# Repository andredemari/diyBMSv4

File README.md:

# ESP32 port of diyBMS v4

This is my port of Stuart Pittaway's excellent diyBMS ver 4 project

In this port the ESP8266 Controller has been replaced by an ESP32 and various changes have been made to support my local needs.
If you are looking for a straight port to ESP32 of Stuart's project, check out the 'Vanilla' branch.
Note: Because of the way serial ports work in ESP32, the Cell module firmware from this fork must be used. Cell modules programmed with the original firmware will not work.

Main changes are :-
* New Controller PCB design with ESP32 module ( a Lolin 32 Lite easily available on AliExpress)
* INA226 Current and Voltage monitor on PCB - INA226 is able to measure current through an external shunt on high or low side of battery. It supports battery voltages of up to 36V,
so since my battery is more than that I put the shunt halfway up the battery stack, and use a voltage divider to measure total battery voltage. INA226 is I2C connected to the ESP32.
https://www.ti.com/lit/ds/symlink/ina226.pdf
* I2C connector to attach to various fan controllers.
* PWM connector to signal discharge rate to my inverter.
* Serial interface to signal charge rate to my BST900 charger [BST900(https://github.com/delboy711/BST900)]
* Two connectors for Solid State Relays to power on/off charger and inverter.
* Management of Controller via MQTT commands from Node-Red.

Stuart's original README follows

##################################################################
 
Version 4 of the diyBMS

Do it yourself battery management system for Lithium ion battery packs/cells

If you are looking for version 3 of this project take a look here https://github.com/stuartpittaway/diyBMS

# TRAVIS-CI

# Videos on how to use and build

https://www.youtube.com/stuartpittaway

# WARNING

This is a DIY product/solution so don’t use this for safety critical systems or in any situation where there could be a risk to life.  

There is no warranty, it may not work as expected or at all.

The use of this project is done so entirely at your own risk.  It may involve electrical voltages which could kill - if in doubt, seek help.

The use of this project may not be compliant with local laws or regulations - if in doubt, seek help.

# License

This work is licensed under a Creative Commons Attribution-NonCommercial-ShareAlike 2.0 UK: England & Wales License.

https://creativecommons.org/licenses/by-nc-sa/2.0/uk/

You are free to:
* Share — copy and redistribute the material in any medium or format
* Adapt — remix, transform, and build upon the material
The licensor cannot revoke these freedoms as long as you follow the license terms.

Under the following terms:
* Attribution — You must give appropriate credit, provide a link to the license, and indicate if changes were made. You may do so in any reasonable manner, but not in any way that suggests the licensor endorses you or your use.
* Non-Commercial — You may not use the material for commercial purposes.
* ShareAlike — If you remix, transform, or build upon the material, you must distribute your contributions under the same license as the original.
* No additional restrictions — You may not apply legal terms or technological measures that legally restrict others from doing anything the license permits.

Notices:
You do not have to comply with the license for elements of the material in the public domain or where your use is permitted by an applicable exception or limitation.

No warranties are given. The license may not give you all of the permissions necessary for your intended use. For example, other rights such as publicity, privacy, or moral rights may limit how you use the material.

# Problem

A DIY Powerwall is the DIY construction of a pack of battery cells to create an energy store which can be used via inverters to power electrical items in the home. Generally cells are salvaged/second hand, and typically use Lithium 18650 cells.

Lithium batteries need to be kept at the same voltage level across a parallel pack. This is done by balancing each cell in the pack to raise or lower its voltage to match the others.

Existing balancing solutions are available in the market place, but at a relatively high cost compared to the cost of the battery bank, so this project is to design a low-cost, simple featured BMS/balancer.

# BMS Design

Design Goals: 
* Build upon my existing skill set and knowledge. 
* Building something that others can contribute to using regular standard libraries and off the shelf components.
* Build something that is inheriently safe
* Use platform.io to manage code and libraries
* Use Arduino based libraries and tools 
* Put everything on GITHUB
* Document it (always gets left to the end!)

# How it works

Controller provides human interface over Wifi/Web and also integrates with other systems like MQTT, emonCMS and Grafana.

Controller is esp8266-12e (NodeMCU v1) - although could be upgraded to ESP32 if really needed.

Controller should be able to take action on alerts/events to shut down inverters/chargers/fuses.

Each cell in a battery pack has a monitoring module.  This uses AVR ATTINY841 linked together by optoisolated serial ports for communication.

ATTINY841 provides:
* internal temperature monitoring
* external temperature monitoring
* Spare input/output for 3rd party use
* autonomous cell voltage balancing - it should still work even if controller is down

# How as v4 improved over v3?

* Code is better!
* Web interface no longer requires access to internet to download javascript libraries
* Controller provides outputs for integration with relay boards and switch gear
* Rules to control relay outputs
* Cell modules use ATTINY841 chip which provides more pins and lower power usage
* Removal of 3.3v regulator and ADUM chips lowers current usage significantly
* v3 module uses 10-12mA current constantly and v4 uses <1mA
* Dual temperature monitoring board + cells

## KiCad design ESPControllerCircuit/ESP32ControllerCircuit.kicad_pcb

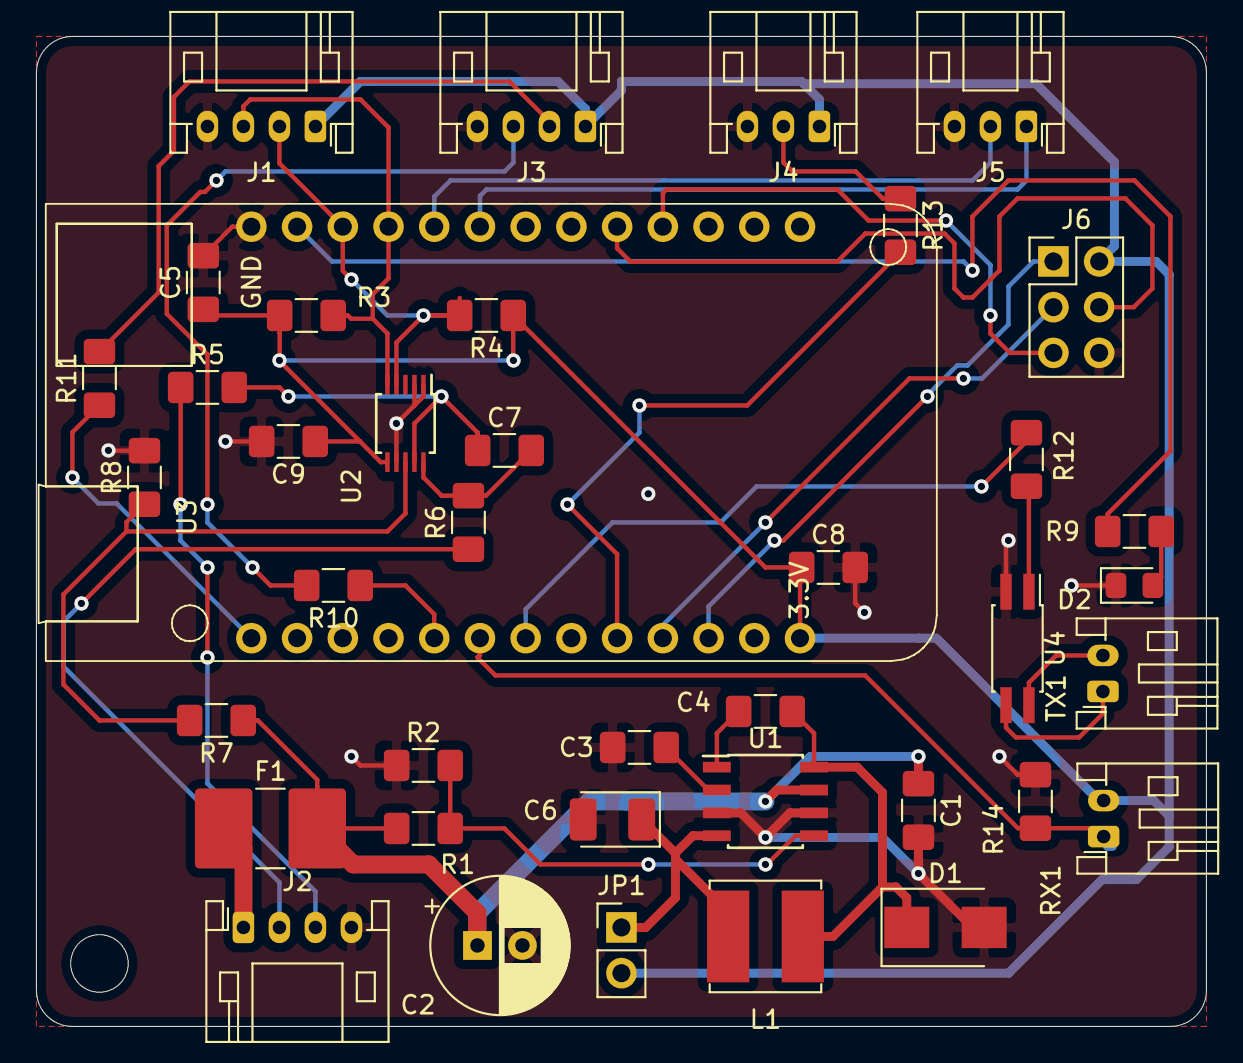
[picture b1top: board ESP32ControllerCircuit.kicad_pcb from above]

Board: 2 copper layers, 65.0 x 55.0 mm, 40 parts (0 on the bottom side), 35 nets.

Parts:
C1, C3, C4, C5, C7, C8, C9: 100nF; C_1206_3216Metric_Pad1.42x1.75mm_HandSolder
C2: 47uF; CP_Radial_D7.5mm_P2.50mm
C6: 47uF Vishay TR3D476K016CO200; CP_EIA-3528-12_Kemet-T_Pad1.50x2.35mm_HandSolder
D1: CD214A-B360LF; D_SMB
D2: COMMS; LED_0805_2012Metric_Pad1.15x1.40mm_HandSolder
F1: 85mA; R_2816_7142Metric_Pad3.20x4.45mm_HandSolder
J1: I2C; JST_PH_S4B-PH-K_1x04_P2.00mm_Horizontal
J2: Battery Sense; JST_PH_S4B-PH-K_1x04_P2.00mm_Horizontal
J3: Inverter/Charger SS Relays; JST_PH_S4B-PH-K_1x04_P2.00mm_Horizontal
J4: Inverter PWM Control; JST_PH_S3B-PH-K_1x03_P2.00mm_Horizontal
J5: BST900 Serial; JST_PH_S3B-PH-K_1x03_P2.00mm_Horizontal
J6: I/O; PinHeader_2x03_P2.54mm_Vertical
JP1: Battery Power; PinHeader_1x02_P2.54mm_Vertical
L1: 150uH; L_Bourns_SRN6045TA
R1: 1M; R_1206_3216Metric_Pad1.42x1.75mm_HandSolder
R2: 390K; R_1206_3216Metric_Pad1.42x1.75mm_HandSolder
R3, R4: 1K; R_1206_3216Metric_Pad1.42x1.75mm_HandSolder
R5, R6: 10R; R_1206_3216Metric_Pad1.42x1.75mm_HandSolder
R7, R8: 100K; R_1206_3216Metric_Pad1.42x1.75mm_HandSolder
R9: 470R; R_1206_3216Metric_Pad1.42x1.75mm_HandSolder
R10, R11: 0R; R_1206_3216Metric_Pad1.42x1.75mm_HandSolder
R12: 220R; R_1206_3216Metric_Pad1.42x1.75mm_HandSolder
R13: 390R; R_1206_3216Metric_Pad1.42x1.75mm_HandSolder
R14: 4K7; R_1206_3216Metric_Pad1.42x1.75mm_HandSolder
RX1: Receive; JST_PH_S2B-PH-K_1x02_P2.00mm_Horizontal
TX1: Transmit; JST_PH_S2B-PH-K_1x02_P2.00mm_Horizontal
U1: MAX5033AASA; SOIC-8_3.9x4.9mm_P1.27mm
U2: INA226; TSSOP-10_3x3mm_P0.5mm
U3: Wemos_LoLin32_Lite; Lolin32_Lite
U4: HMHA2801; SO-4_4.4x2.3mm_P1.27mm

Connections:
+3V3: C5.1, C8.1, C9.1, J1.1, J3.1, J4.1, J6.2, JP1.2, R3.1, R4.1, RX1.2, U2.6, U3.26
+BATT: C1.1, C2.1, F1.2, R1.2, R7.1, U1.7
CHARGER: R10.1, U3.18
GND: C1.2, C2.2, C3.2, C5.2, C6.2, C8.2, C9.2, D1.2, D2.1, J1.4, J2.4, J3.4, J4.3, J5.3, J6.6, R2.1, R8.2, R14.1, U1.3, U1.6, U2.1, U2.2, U2.7, U3.13, U4.2
GPIO19: J6.1, U3.24
GPIO23: J6.3, U3.23
GPIO34: J6.5, U3.4
GPIO35: J6.4, U3.5
INVERTER: R11.1, U3.14
InverterPWM: R13.2, U3.22
unnamed: C3.1, U1.2
unnamed: C4.1, D1.1, L1.1, U1.8
unnamed: C4.2, U1.1
unnamed: C6.1, JP1.1, L1.2, U1.4
unnamed: D2.2, R9.1
unnamed: F1.1, J2.1
unnamed: J2.2, R6.1
unnamed: J2.3, R5.1
unnamed: J3.2, R11.2
unnamed: J3.3, R10.2
unnamed: J4.2, R13.1
unnamed: R1.1, R2.2, U1.5
unnamed: R9.2, U3.12
unnamed: R12.1, U4.1
unnamed: R12.2, U3.20
unnamed: R14.2, RX1.1, U3.19
unnamed: TX1.1, U4.3
unnamed: TX1.2, U4.4
RX1: J5.2, U3.9
SCL: J1.3, R3.2, U2.5, U3.10
SDA: J1.2, R4.2, U2.4, U3.11
SHUNT+: C7.2, R6.2, U2.10
SHUNT-: C7.1, R5.2, U2.9
TX1: J5.1, U3.8
VBUS: R7.2, R8.1, U2.8

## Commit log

2019-12-15 Port to ESP32
2019-12-15 One MQTT JSON message per module
2019-12-15 Add command for volatile settings + fixes * Command added to write settings without save to EEPROM * Bugfix to prevent Out of Sequence Errors * PlatformIO upload using Arduino as ISP
2019-12-15 Added ESP32 Circuit PCB
2019-12-16 First MQTT Commands added
2019-12-17 Relay Control by MQTT * More mqtt commands implemented * control of charging and discharging via mqtt
2019-12-17 Doc update
2019-12-17 Control of BST900 boost converter
2019-12-17 Fix compiler warning errors about data types
2019-12-17 Comment tidy up
2019-12-17 Change framing marker from zero to another byte which should reduce the overhead on the data packets which contain a lot of zeros
2019-12-17 Frame marker to zero
2019-12-17 Label Serial1 ports
2019-12-17 Remove debug code and tweak PID settings
2019-12-17 Test program for PID calibration
2019-12-17 Reapply fix for communication with ESP32
2019-12-19 use different pins for I2C
2019-12-20 Add INA226 Voltage/Current/Power Sensor support * Partial implementation of home brew I2C PWM fan controller * Partial implementation of home brew I2C AC power monitor
2019-12-21 Replace EEPROM library with 'Preferences' library * There were issues with EEPROM corruption when resetting with push button.
2019-12-21 Neater 'Preferences' functions
2019-12-31 Allow different nominal R of Int and Ext NTC
2020-01-16 Fix repeating packets bug
2020-02-01 Add new relay rule for mqtt control
